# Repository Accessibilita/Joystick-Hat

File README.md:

# Joystick-HID (0.2a)
A custom open source PCB for controlling an open source wheel chair! This PCB contains all the necessary electronics for interfacing and powering all the components/peripherals that will be used to build a wheel chair human machine interface consisting of this PCB, analog JoyStick module, buttons, rotary switches, and 3D printed housing. JoyStick-HID is just one of the many PCBs being developed for our open source wheel chair electrical system we are developing with the Accessibilita project for the Mobility Independence Foundation (themif.org) !!

Functional Block Diagram of Board 

Quick Specs of the Hat:
- STM32F446RET6 100TQFP ARM Cortex M4 Microcontoller
- ARM Cortex M Serial Debu Interface/connector for in system programming and development 
- MAX3535ECWI+T RS485 Transceiver for communicating with main motor controller
- D24V22F5 2.5A 5VDC Voltage Regulator Module
- D24V22F3 2.5A 3.3VDC Voltage Regulator Module
- 24V Power Input with High Current Pheonix Contact Connector
- 8 Debug LEDs for STM32F446RET6
- Onboard Battery for STM32F446RET6 RealTime Clock
- Interface for JoyStick, JH-D202X-R2/R4 Joystick 5K https://protosupplies.com/product/jh-d202x-r2-r4-joystick-5k/
- Interface for two Rotary Switches
- Interface for 8 Momentary swiches/buttons
- Interface for LED driver board, this additional board drives LEDs in the arm wrest indicating battery level and current set speed
- STM32 will run FreeRTOS w/ Custom Processes written for all functionality with priority scheduling for safety rated functions.

This hat is intended as a developmental platform that can function in the field, it has all the features needed to control the wheel chair with additional feature that will make software development easier. The final version will be much simpler and low cost, this is only the beginning. 

2D Render of JoyStick-HID Hat in KiCAD 8.0

3D Renders of JoyStick-HID Hat in KiCAD 8.0 3D Viewer 

# Joystick-Hat (0.1a)
Version 0.1a JoyStick HID:

RPi Hat for controlling an open source wheel chair! This hat contains all the necessary electronics for interfacing and powering all the components/peripherals that will be used to control the open source wheel chair electrical system we are developing with the Accessibilita project !!

Functional Block Diagram of Board 

Quick Specs of the Hat:
- STM32F446RET6 100TQFP ARM Cortex M4 Microcontoller
- ARM Cortex M Serial Debu Interface/connector for in system programming and development 
- MAX3535ECWI+T RS485 Transceiver for communicating with main motor controller
- D24V22F5 2.5A 5VDC Voltage Regulator Module
- D24V22F3 2.5A 3.3VDC Voltage Regulator Module
- D24V22F12 2.5A 12VDC Voltage Regulator Module
- 24V Power Input with High Current Pheonix Contact Connector
- 12V Power output with High current Phoenix Contact Connector
- Rapsberry Pi 5 Running ROS2, directly power via header from 5VDC rail
- 8 Debug LEDs for STM32F446RET6
- 8 Debug LEDs for RPi 5
- Onboard Battery for STM32F446RET6 RealTime Clock
- Interface for JoyStick, JH-D202X-R2/R4 Joystick 5K https://protosupplies.com/product/jh-d202x-r2-r4-joystick-5k/
- Interface for two Rotary Switches
- Interface for 8 Momentary swiches/buttons
- Interface for LED driver board, this additional board drives LEDs in the arm wrest indicating battery level and current set speed
- STM32 will run custom FreeRTOS or ROS-Micro more to follow

This hat is intended as a developmental platform that can function in the field, it has all the features needed to control the wheel chair with additional feature that will make software development easier. The final version will be much simpler and low cost, this is only the beginning. 

2D Render of JoyStick-HID Hat in KiCAD 8.0

3D Renders of JoyStick-HID Hat in KiCAD 8.0 3D Viewer 

# Joystick-Hat (0.1a) Prototype Assembly and Test:

Notes:
assmbely notes:
- Footprint for Raspberry Pi Header connector is wrong, its 42 pins should be 40
- 10uF caps on input = footprint too small!
- C19 footprint too big
- Max chip Pin 1 legend too hard to see
- RS485 diode orientation legend not on PCB
- STM32 Pin 1 legend not there
- Header holes for DCDC regulator modules too small had to hack them on there.
- ARM Cortex M Debug Connector issues, signals are flipped around, the footprint numbering doesn't correspond to the symbol numbering.
- All DCDC Regulators Work and produce correct voltage
- Debug LEDs Work
- GPIO and ADC Interfaces Work

Firmware:
Test firmware along with instructions on how to build and run can be found here: https://github.com/Accessibilita/JoyStick-hat-firmware

## Photos 

Version 0.1a of PCB 90% of Assembled and ready for programming test

Fix for the flpped programming interface from the symbol/footprint number error

Board Hooked Up to Programming Interface with soldered on fix 

Board Powered Up Running Code

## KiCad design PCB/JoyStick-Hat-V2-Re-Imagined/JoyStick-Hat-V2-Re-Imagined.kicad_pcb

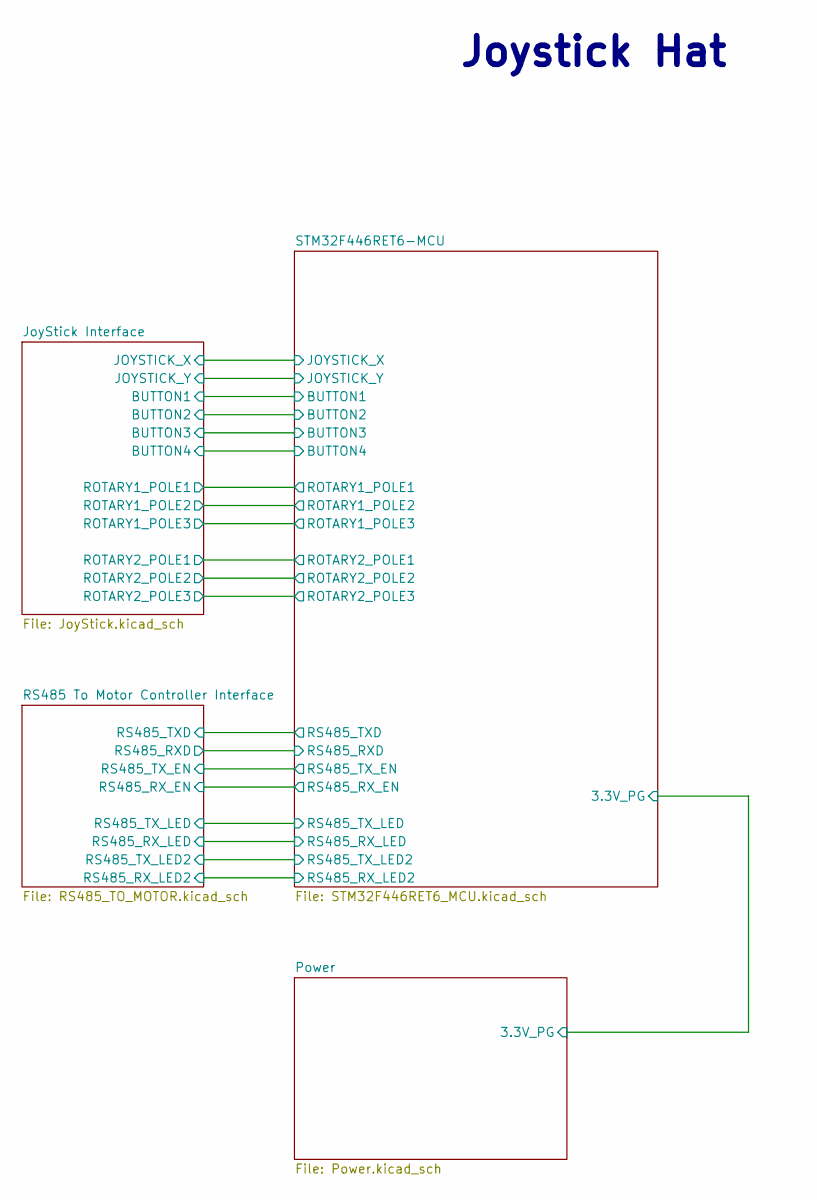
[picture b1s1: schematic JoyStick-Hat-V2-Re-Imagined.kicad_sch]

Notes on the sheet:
Joystick Hat

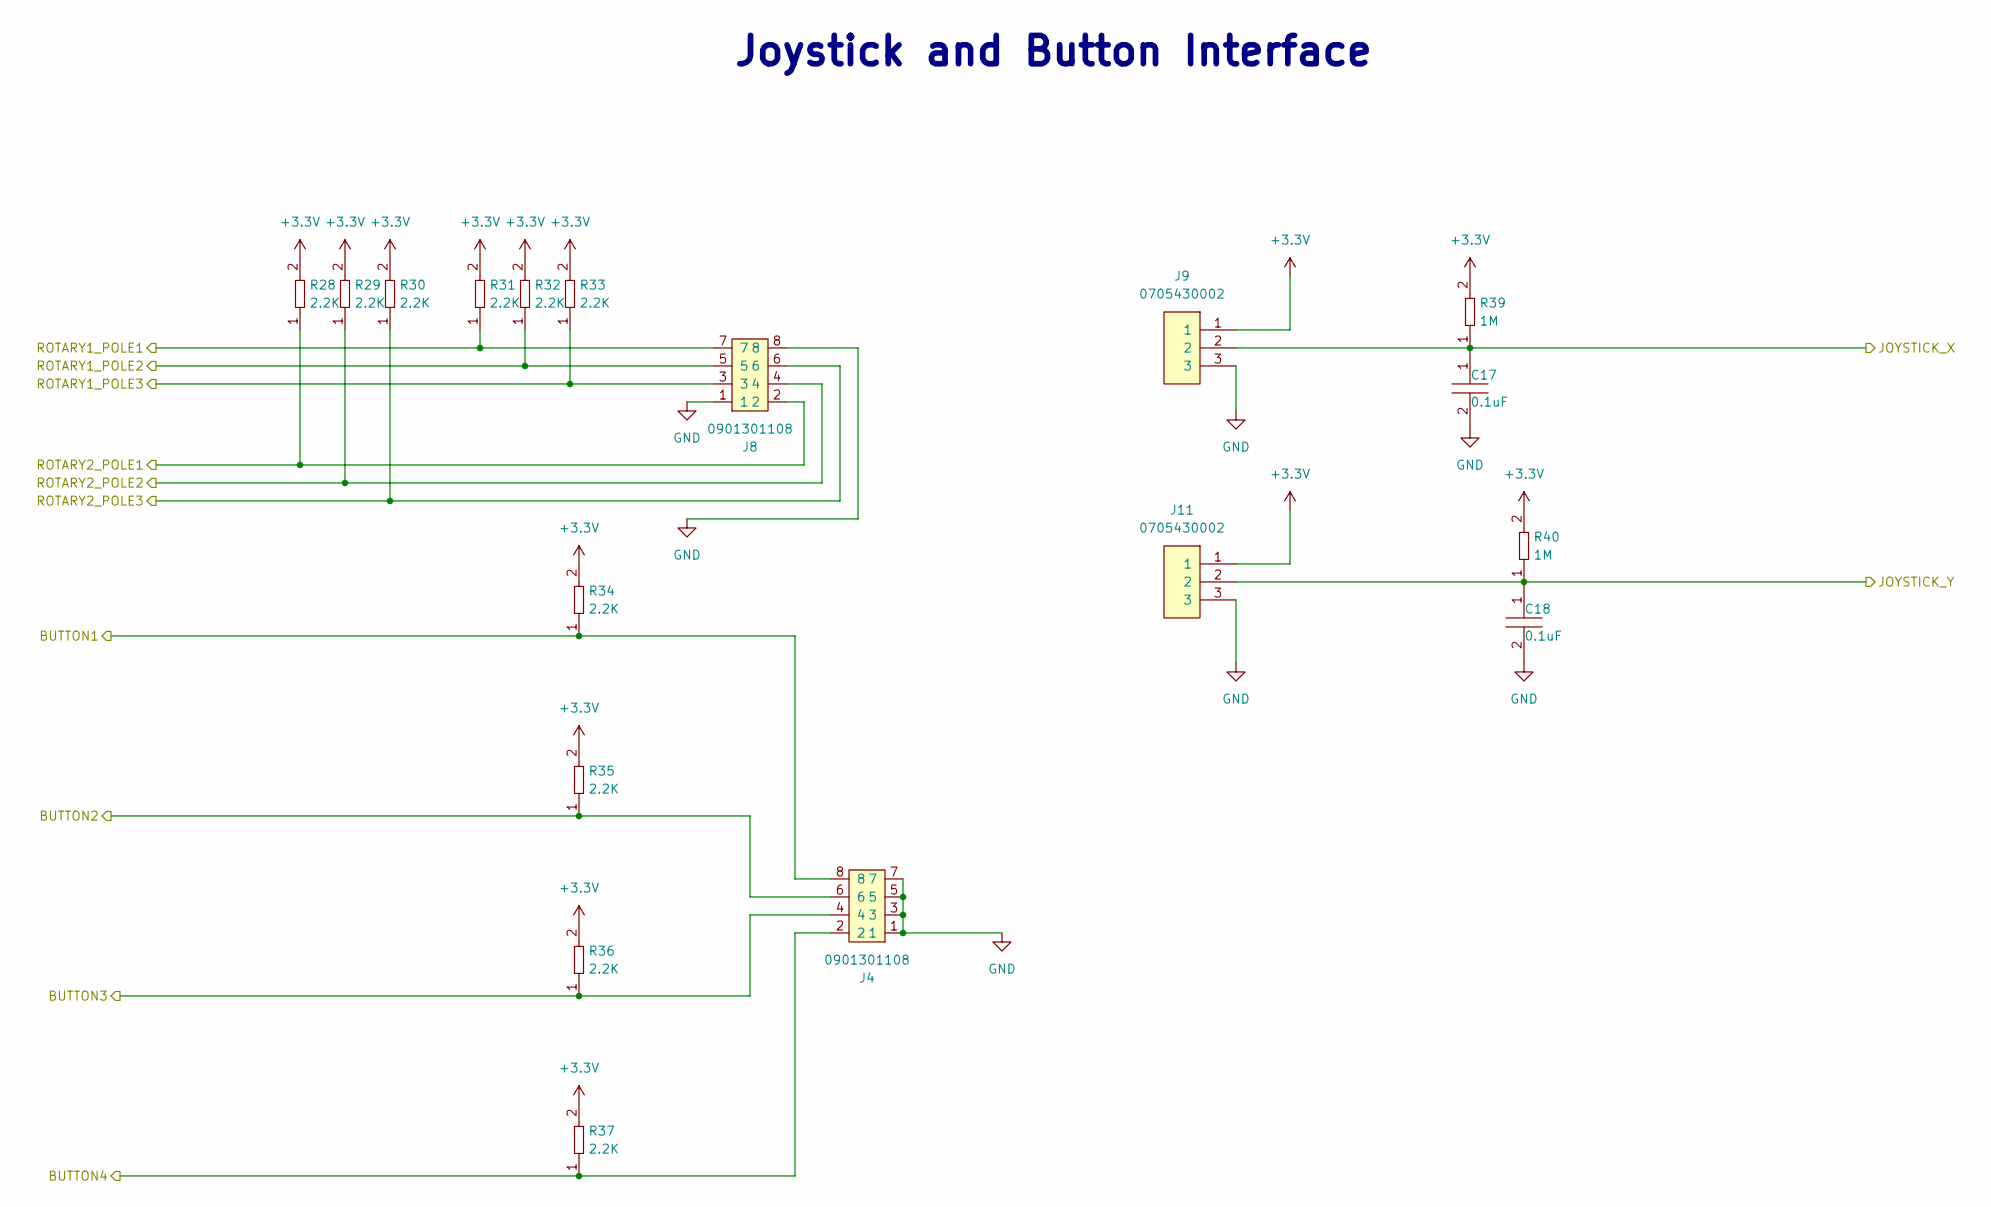
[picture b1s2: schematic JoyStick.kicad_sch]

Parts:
C17, C18: C0402C104K9PACTU; R0402; Tolerance 10%; Voltage 6.3V; MFR# C0402C104K9PACTU
J4, J8: 0901301108; CON_901301108_MOL; Tolerance *; Voltage *; MFR# 0901301108
J9, J11: 0705430002; Shrouded_Pin_Header_Straight_1x03_Pitch2.54mm; Tolerance *; Voltage 250V; MFR# 0705430002
R28, R29, R30, R31, R32, R33, R34, R35, R36, R37: RC0402FR-072K2L; R0402; Tolerance 1%; Voltage N/A; MFR# RC0402FR-072K2L
R39, R40: RT0603BRD071ML; R0603; Tolerance 1%; Voltage N/A; MFR# RT0603BRD071ML

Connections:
+3.3V: J9.1, J11.1, R28.2, R29.2, R30.2, R31.2, R32.2, R33.2, R34.2, R35.2, R36.2, R37.2, R39.2, R40.2; also elsewhere on the board
/JoyStick Interface/BUTTON1: J4.8, R34.1; also elsewhere on the board
/JoyStick Interface/BUTTON2: J4.6, R35.1; also elsewhere on the board
/JoyStick Interface/BUTTON3: J4.4, R36.1; also elsewhere on the board
/JoyStick Interface/BUTTON4: J4.2, R37.1; also elsewhere on the board
/JoyStick Interface/JOYSTICK_X: C17.1, J9.2, R39.1; also elsewhere on the board
/JoyStick Interface/JOYSTICK_Y: C18.1, J11.2, R40.1; also elsewhere on the board
/JoyStick Interface/ROTARY1_POLE1: J8.7, R31.1; also elsewhere on the board
/JoyStick Interface/ROTARY1_POLE2: J8.5, R32.1; also elsewhere on the board
/JoyStick Interface/ROTARY1_POLE3: J8.3, R33.1; also elsewhere on the board
/JoyStick Interface/ROTARY2_POLE1: J8.2, R28.1; also elsewhere on the board
/JoyStick Interface/ROTARY2_POLE2: J8.4, R29.1; also elsewhere on the board
/JoyStick Interface/ROTARY2_POLE3: J8.6, R30.1; also elsewhere on the board
GND: C17.2, C18.2, J4.1, J4.3, J4.5, J4.7, J8.1, J8.8, J9.3, J11.3; also elsewhere on the board

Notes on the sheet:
Joystick and Button Interface

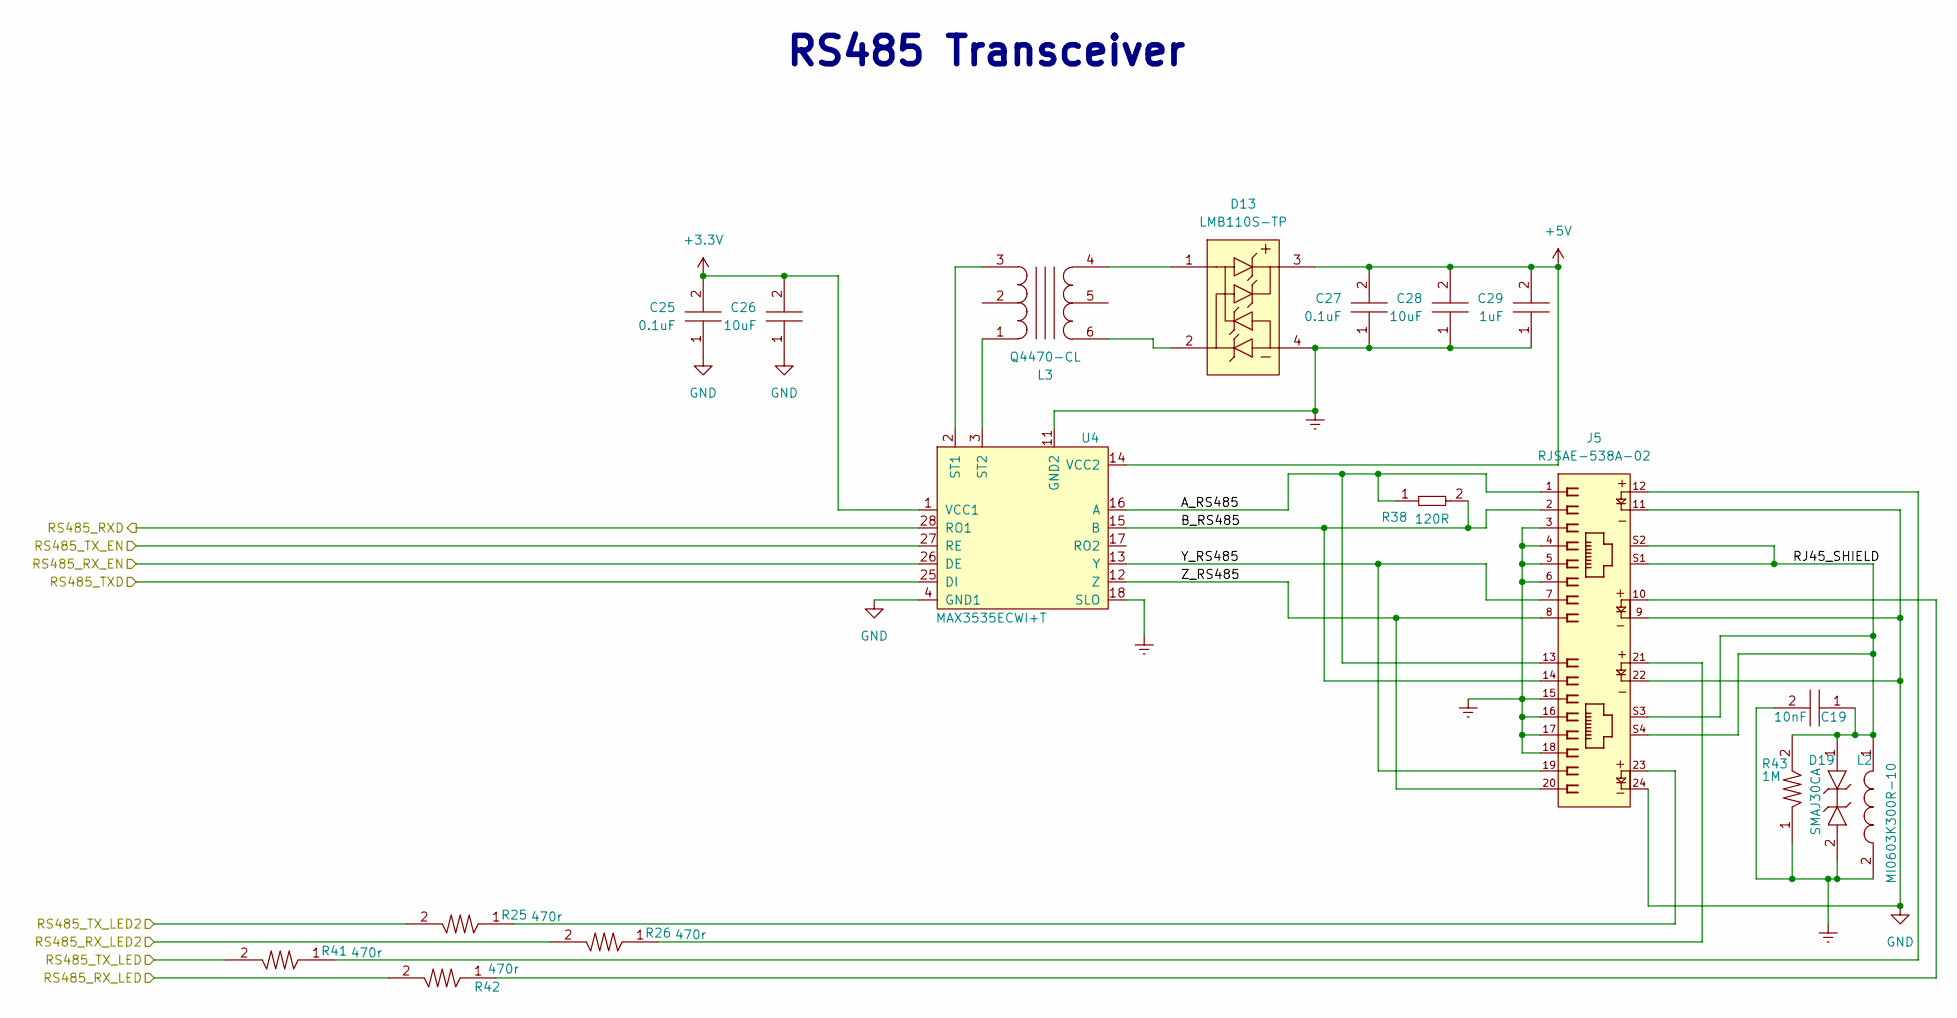
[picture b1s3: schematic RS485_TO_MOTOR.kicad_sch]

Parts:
C19: C0805C103KCRACAUTO; C0805; Tolerance 10%; Voltage 500V; MFR# C0805C103KCRACAUTO
C25, C27: CL10B104JB8NNNC; C0603; Tolerance 5%; Voltage 50V; MFR# CL10B104JB8NNNC
C26, C28: CGA5L3X5R1V106K160AB; C1206; Tolerance 10%; Voltage 35V; MFR# CGA5L3X5R1V106K160AB
C29: C1206C105K3RACAUTO; D_SOD-123; Tolerance 10%; Voltage 25V; MFR# C1206C105K3RACAUTO
D13: LMB110S-TP; Tolerance *; Voltage 850 mV @ 500 mA; MFR# LMB110S-TP
D19: SMAJ30CA; Tolerance *; Voltage 30V Clamp; MFR# SMAJ30CA
J5: RJSAE-538A-02; AMPHENOL_RJSAE538A02; Tolerance N/A; Voltage *; MFR# RJSAE-538A-02
L2: MI0603K300R-10; Tolerance *; Voltage *; MFR# MI0603K300R-10
L3: Q4470-CL; SO6_Q4470-CL_C-SIZE_COC; Tolerance *; Voltage 5V; MFR# Q4470-CL
R25, R26, R41, R42: RC0603FR-07470RL; R0603; Tolerance 1%; Voltage *; MFR# RC0603FR-07470RL
R38: AC0402FR-07120RL; R0402; Tolerance 1%; Voltage *; MFR# AC0402FR-07120RL
R43: RC1206FR-071ML; R1206; Tolerance 1%; Voltage *; MFR# RC1206FR-071ML
U4: MAX3535ECWI+T; 21-0145_W28M&plus_9_MXM; Tolerance N/A; Voltage 3-5.5V; MFR# MAX3535ECWI+T

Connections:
+3.3V: C25.2, C26.2, U4.1 (VCC1); also elsewhere on the board
+5V: C27.2, C28.2, C29.2, D13.3, U4.14 (VCC2)
/RS485 To Motor Controller Interface/A_RS485: J5.1, J5.13, R38.1, U4.16 (A)
/RS485 To Motor Controller Interface/B_RS485: J5.2, J5.14, R38.2, U4.15 (B)
/RS485 To Motor Controller Interface/RJ45_SHIELD: C19.1, D19.1, J5.S1, J5.S2, J5.S3, J5.S4, L2.1, R43.2
/RS485 To Motor Controller Interface/RS485_RXD: U4.28 (RO1); also elsewhere on the board
/RS485 To Motor Controller Interface/RS485_RX_EN: U4.26 (DE); also elsewhere on the board
/RS485 To Motor Controller Interface/RS485_RX_LED: R42.2; also elsewhere on the board
/RS485 To Motor Controller Interface/RS485_RX_LED2: R26.2; also elsewhere on the board
/RS485 To Motor Controller Interface/RS485_TXD: U4.25 (DI); also elsewhere on the board
/RS485 To Motor Controller Interface/RS485_TX_EN: U4.27 (RE); also elsewhere on the board
/RS485 To Motor Controller Interface/RS485_TX_LED: R41.2; also elsewhere on the board
/RS485 To Motor Controller Interface/RS485_TX_LED2: R25.2; also elsewhere on the board
/RS485 To Motor Controller Interface/Y_RS485: J5.7, J5.19, U4.13 (Y)
/RS485 To Motor Controller Interface/Z_RS485: J5.8, J5.20, U4.12 (Z)
Earth: C19.2, C27.1, C28.1, C29.1, D13.4, D19.2, J5.3, J5.4, J5.5, J5.6, J5.15, J5.16, J5.17, J5.18, L2.2, R43.1, U4.11 (GND2), U4.18 (SLO)
GND: C25.1, C26.1, J5.9, J5.11, J5.22, J5.24, U4.4 (GND1); also elsewhere on the board
unnamed: D13.1, L3.4
unnamed: D13.2, L3.6
unnamed: J5.10, R42.1
unnamed: J5.12, R41.1
unnamed: J5.21, R26.1
unnamed: J5.23, R25.1
unnamed: L3.3, U4.2 (ST1)
unnamed: L3.1, U4.3 (ST2)

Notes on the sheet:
RS485 Transceiver

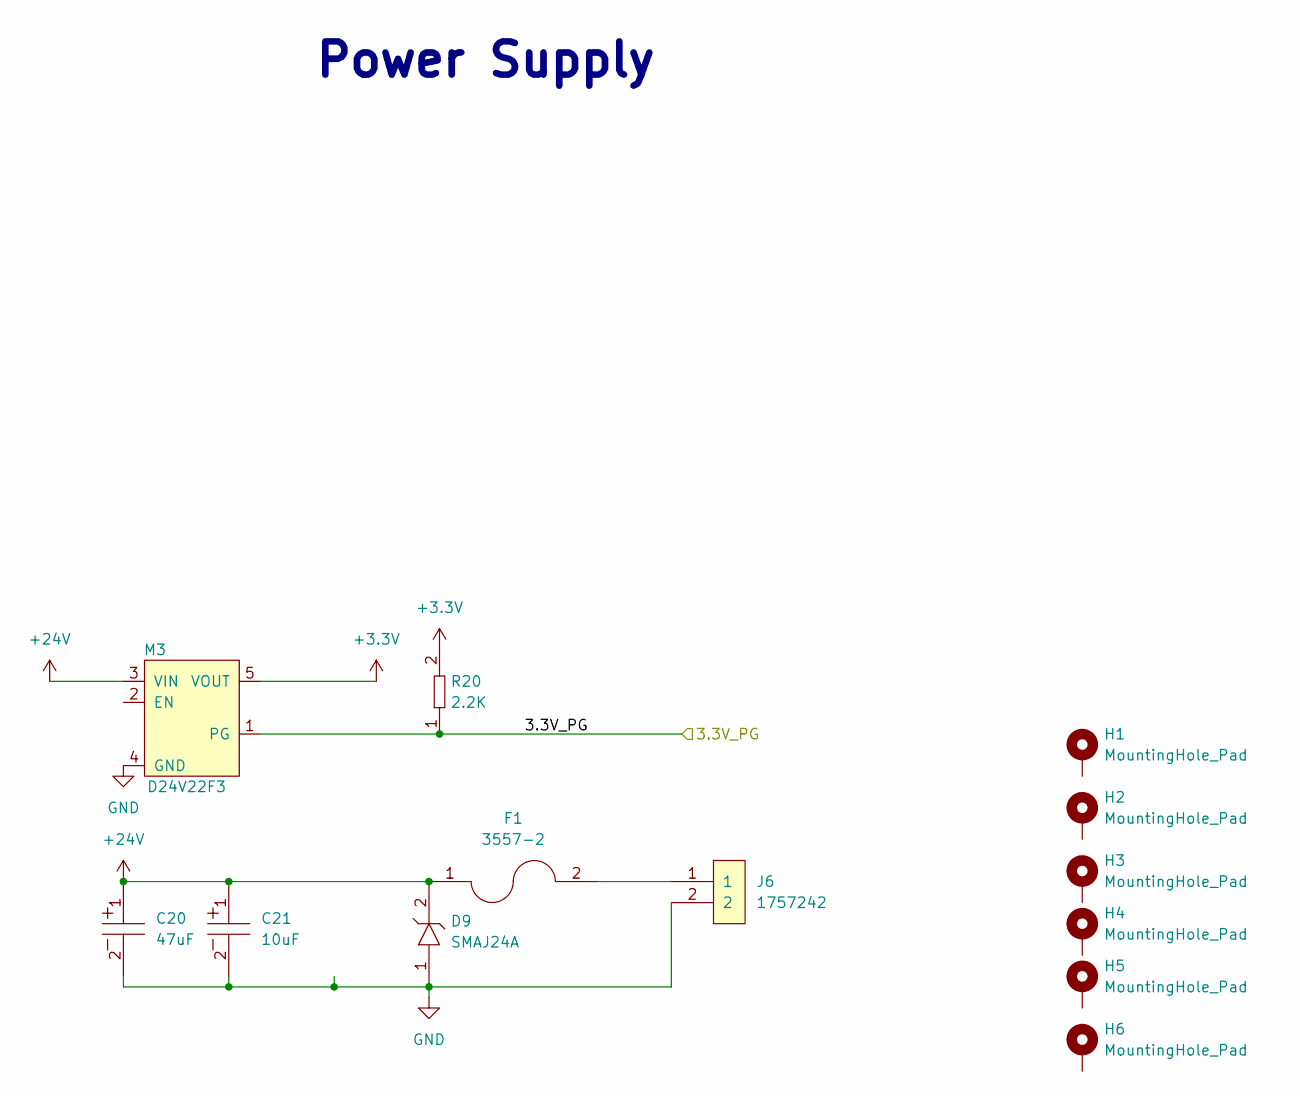
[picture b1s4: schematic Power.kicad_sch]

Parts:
C20: UUQ1H470MCL1GS; CP_Elec_8x10; Tolerance 20%; Voltage 50V; MFR# UUQ1H470MCL1GS
C21: UUQ1H100MCL1GB; CAP_UUQ_6P3X5P4_NCH; Tolerance 20%; Voltage 50V; MFR# UUQ1H100MCL1GB
D9: SMAJ24A; SMAJ; Tolerance *; Voltage 24V RS, 26.7V VB, 38.9V Clamp; MFR# SMAJ24A
F1: 3557-2; FUSE_3557-2; Tolerance *; Voltage 500V; MFR# 3557-2
H1, H2, H3, H4, H5, H6: MountingHole_Pad; RPI_HAT_HOLE
J6: 1757242; PhoenixContact_MSTBA-G_02x5.08mm_Angled; Tolerance *; Voltage 300V; MFR# 1757242
M3: D24V22F3; D24V22F12; Tolerance N/A; Voltage 36V IN 3.3V OUT; MFR# D24V22F3
R20: RC0603FR-072K2L; R0603; Tolerance 1%; Voltage N/A; MFR# RC0603FR-072K2L

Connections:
+3.3V: M3.5 (VOUT), R20.2; also elsewhere on the board
+24V: C20.1, C21.1, D9.2, F1.1, M3.3 (VIN)
/Power/3.3V_PG: M3.1 (PG), R20.1; also elsewhere on the board
GND: C20.2, C21.2, D9.1, J6.2, M3.4 (GND); also elsewhere on the board
unnamed: F1.2, J6.1

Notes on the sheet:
Power Supply

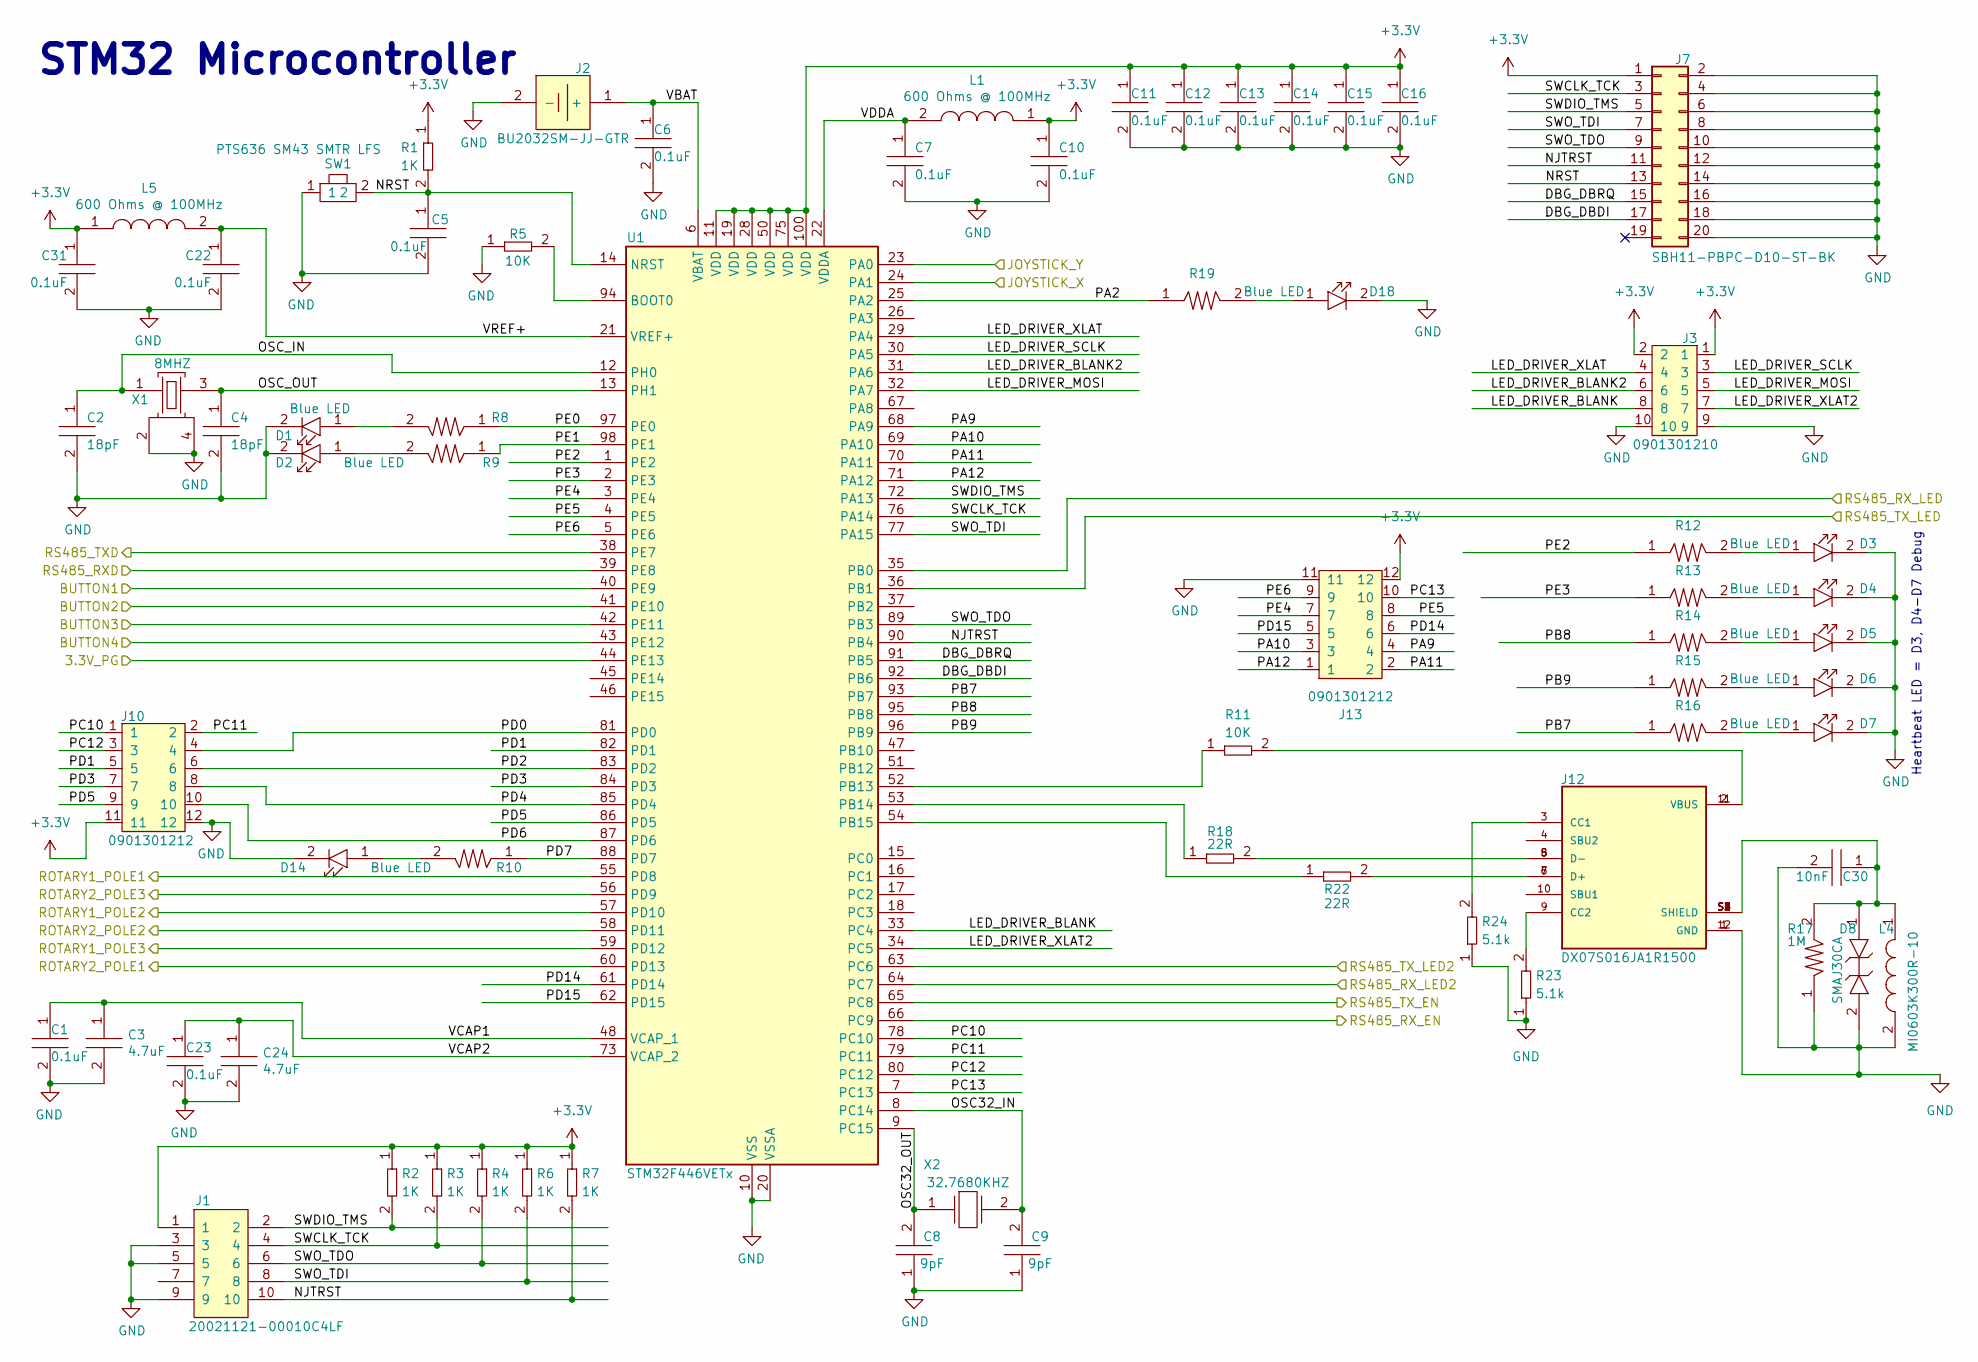
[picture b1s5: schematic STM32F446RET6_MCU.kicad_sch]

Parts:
C1, C5, C6, C7, C10, C11, C12, C13, C14, C15, C16, C22, C23, C31: C0402C104K9PACTU; R0402; Tolerance 10%; Voltage 6.3V; MFR# C0402C104K9PACTU
C2, C4: GCM1555C1H180GA16D; C0402; Tolerance 2%; Voltage 50V; MFR# GCM1555C1H180GA16D
C3, C24: GRM155R60J475ME47D; C0402; Tolerance 20%; Voltage 6.3V; MFR# GRM155R60J475ME47D
C8, C9: CL05C090CB5NNNC; C0402; Tolerance ±0.25pF; Voltage 50V; MFR# CL05C090CB5NNNC
C30: C0805C103KCRACAUTO; C0805; Tolerance 10%; Voltage 500V; MFR# C0805C103KCRACAUTO
D1, D2, D3, D4, D5, D6, D7, D14, D18: LTST-C194TBKT; LED0603; Tolerance *; Voltage 3.3V; MFR# LTST-C194TBKT
D8: SMAJ30CA; Tolerance *; Voltage 30V Clamp; MFR# SMAJ30CA
J1: 20021121-00010C4LF; Tolerance *; Voltage *; MFR# 20021121-00010C4LF
J2: BU2032SM-JJ-GTR; Tolerance *; Voltage 3.3V; MFR# BU2032SM-JJ-GTR
J3: 0901301210; CON_901301210_MOL; Tolerance *; Voltage *; MFR# 0901301210
J7: SBH11-PBPC-D10-ST-BK; SULLINS_SBH11-PBPC-D10-ST-BK; Tolerance *; Voltage *; MFR# SBH11-PBPC-D10-ST-BK
J10, J13: 0901301212; CON_901301212_MOL; Tolerance *; Voltage *; MFR# 0901301212
J12: DX07S016JA1R1500; JAE_DX07S016JA1R1500; Tolerance *; Voltage 20V; MFR# DX07S016JA1R1500
L1, L5: BLM15HG601SN1D; Tolerance *; Voltage *; MFR# BLM15HG601SN1D
L4: MI0603K300R-10; Tolerance *; Voltage *; MFR# MI0603K300R-10
R1, R2, R3, R4, R6, R7: RC0402FR-071KL; R0402; Tolerance 1%; Voltage *; MFR# RC0402FR-071KL
R5, R11: RC0402FR-0710KL; R0402; Tolerance 1%; Voltage *; MFR# RC0402FR-0710KL
R8, R9, R10, R12, R13, R14, R15, R16, R19: RC0603FR-07470RL; R0603; Tolerance 1%; Voltage *; MFR# RC0603FR-07470RL
R17: RC1206FR-071ML; R1206; Tolerance 1%; Voltage *; MFR# RC1206FR-071ML
R18, R22: RC0402FR-0722RL; R0402; Tolerance 1%; Voltage *; MFR# RC0402FR-0722RL
R23, R24: RC0402FR-075K1L; R0402; Tolerance 1%; Voltage N/A; MFR# RC0402FR-075K1L
SW1: PTS636 SM43 SMTR LFS; Tolerance *; Voltage 12V; MFR# PTS636 SM43 SMTR LFS
U1: STM32F446VETx; LQFP-100_14x14mm_P0.5mm
X1: ABM3B-8.000MHZ-B2-T; ABM3B8.000MHZB2T; Tolerance *; Voltage *; MFR# ABM3B-8.000MHZ-B2-T
X2: ABS07-32.768KHZ-9-T; Tolerance *; Voltage *; MFR# ABS07-32.768KHZ-9-T

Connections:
+3.3V: C10.1, C11.1, C12.1, C13.1, C14.1, C15.1, C16.1, C31.1, J1.1, J3.1, J3.2, J7.1, J10.11, J13.12, L1.1, L5.1, R1.1, R2.1, R3.1, R4.1, R6.1, R7.1, U1.11 (VDD), U1.19 (VDD), U1.28 (VDD), U1.50 (VDD), U1.75 (VDD), U1.100 (VDD); also elsewhere on the board
/JoyStick Interface/BUTTON1: U1.40 (PE9); also elsewhere on the board
/JoyStick Interface/BUTTON2: U1.41 (PE10); also elsewhere on the board
/JoyStick Interface/BUTTON3: U1.42 (PE11); also elsewhere on the board
/JoyStick Interface/BUTTON4: U1.43 (PE12); also elsewhere on the board
/JoyStick Interface/JOYSTICK_X: U1.24 (PA1); also elsewhere on the board
/JoyStick Interface/JOYSTICK_Y: U1.23 (PA0); also elsewhere on the board
/JoyStick Interface/ROTARY1_POLE1: U1.55 (PD8); also elsewhere on the board
/JoyStick Interface/ROTARY1_POLE2: U1.57 (PD10); also elsewhere on the board
/JoyStick Interface/ROTARY1_POLE3: U1.59 (PD12); also elsewhere on the board
/JoyStick Interface/ROTARY2_POLE1: U1.60 (PD13); also elsewhere on the board
/JoyStick Interface/ROTARY2_POLE2: U1.58 (PD11); also elsewhere on the board
/JoyStick Interface/ROTARY2_POLE3: U1.56 (PD9); also elsewhere on the board
/Power/3.3V_PG: U1.44 (PE13); also elsewhere on the board
/RS485 To Motor Controller Interface/RS485_RXD: U1.39 (PE8); also elsewhere on the board
/RS485 To Motor Controller Interface/RS485_RX_EN: U1.66 (PC9); also elsewhere on the board
/RS485 To Motor Controller Interface/RS485_RX_LED: U1.35 (PB0); also elsewhere on the board
/RS485 To Motor Controller Interface/RS485_RX_LED2: U1.64 (PC7); also elsewhere on the board
/RS485 To Motor Controller Interface/RS485_TXD: U1.38 (PE7); also elsewhere on the board
/RS485 To Motor Controller Interface/RS485_TX_EN: U1.65 (PC8); also elsewhere on the board
/RS485 To Motor Controller Interface/RS485_TX_LED: U1.36 (PB1); also elsewhere on the board
/RS485 To Motor Controller Interface/RS485_TX_LED2: U1.63 (PC6); also elsewhere on the board
/STM32F446RET6-MCU/5V_PG: U1.45 (PE14)
/STM32F446RET6-MCU/12V_PG: U1.46 (PE15)
/STM32F446RET6-MCU/DBG_DBDI: J7.17, U1.92 (PB6)
/STM32F446RET6-MCU/DBG_DBRQ: J7.15, U1.91 (PB5)
/STM32F446RET6-MCU/LED_DRIVER_BLANK: J3.8, U1.33 (PC4)
/STM32F446RET6-MCU/LED_DRIVER_BLANK2: J3.6, U1.31 (PA6)
/STM32F446RET6-MCU/LED_DRIVER_MOSI: J3.5, U1.32 (PA7)
/STM32F446RET6-MCU/LED_DRIVER_SCLK: J3.3, U1.30 (PA5)
/STM32F446RET6-MCU/LED_DRIVER_XLAT: J3.4, U1.29 (PA4)
/STM32F446RET6-MCU/LED_DRIVER_XLAT2: J3.7, U1.34 (PC5)
/STM32F446RET6-MCU/NJTRST: J1.10, J7.11, R7.2, U1.90 (PB4)
/STM32F446RET6-MCU/NRST: C5.1, J7.13, R1.2, SW1.2, U1.14 (NRST)
/STM32F446RET6-MCU/OSC32_IN: C9.2, U1.8 (PC14), X2.2
/STM32F446RET6-MCU/OSC32_OUT: C8.2, U1.9 (PC15), X2.1
/STM32F446RET6-MCU/OSC_IN: C2.1, U1.12 (PH0), X1.1
/STM32F446RET6-MCU/OSC_OUT: C4.1, U1.13 (PH1), X1.3
/STM32F446RET6-MCU/PA2: R19.1, U1.25 (PA2)
/STM32F446RET6-MCU/PA9: J13.4, U1.68 (PA9)
/STM32F446RET6-MCU/PA10: J13.3, U1.69 (PA10)
/STM32F446RET6-MCU/PA11: J13.2, U1.70 (PA11)
/STM32F446RET6-MCU/PA12: J13.1, U1.71 (PA12)
/STM32F446RET6-MCU/PB7: R16.1, U1.93 (PB7)
/STM32F446RET6-MCU/PB8: R14.1, U1.95 (PB8)
/STM32F446RET6-MCU/PB9: R15.1, U1.96 (PB9)
/STM32F446RET6-MCU/PC10: J10.1, U1.78 (PC10)
/STM32F446RET6-MCU/PC11: J10.2, U1.79 (PC11)
/STM32F446RET6-MCU/PC12: J10.3, U1.80 (PC12)
/STM32F446RET6-MCU/PC13: J13.10, U1.7 (PC13)
/STM32F446RET6-MCU/PD0: J10.4, U1.81 (PD0)
/STM32F446RET6-MCU/PD1: J10.5, U1.82 (PD1)
/STM32F446RET6-MCU/PD2: J10.6, U1.83 (PD2)
/STM32F446RET6-MCU/PD3: J10.7, U1.84 (PD3)
/STM32F446RET6-MCU/PD4: J10.8, U1.85 (PD4)
/STM32F446RET6-MCU/PD5: J10.9, U1.86 (PD5)
/STM32F446RET6-MCU/PD6: J10.10, U1.87 (PD6)
/STM32F446RET6-MCU/PD7: R10.1, U1.88 (PD7)
/STM32F446RET6-MCU/PD14: J13.6, U1.61 (PD14)
/STM32F446RET6-MCU/PD15: J13.5, U1.62 (PD15)
/STM32F446RET6-MCU/PE0: R8.1, U1.97 (PE0)
/STM32F446RET6-MCU/PE1: R9.1, U1.98 (PE1)
/STM32F446RET6-MCU/PE2: R12.1, U1.1 (PE2)
/STM32F446RET6-MCU/PE3: R13.1, U1.2 (PE3)
/STM32F446RET6-MCU/PE4: J13.7, U1.3 (PE4)
/STM32F446RET6-MCU/PE5: J13.8, U1.4 (PE5)
/STM32F446RET6-MCU/PE6: J13.9, U1.5 (PE6)
/STM32F446RET6-MCU/SWCLK_TCK: J1.4, J7.3, R3.2, U1.76 (PA14)
/STM32F446RET6-MCU/SWDIO_TMS: J1.2, J7.5, R2.2, U1.72 (PA13)
/STM32F446RET6-MCU/SWO_TDI: J1.8, J7.7, R6.2, U1.77 (PA15)
/STM32F446RET6-MCU/SWO_TDO: J1.6, J7.9, R4.2, U1.89 (PB3)
/STM32F446RET6-MCU/VBAT: C6.1, J2.1 (+), U1.6 (VBAT)
/STM32F446RET6-MCU/VCAP1: C1.1, C3.1, U1.48 (VCAP_1)
/STM32F446RET6-MCU/VCAP2: C23.1, C24.1, U1.73 (VCAP_2)
/STM32F446RET6-MCU/VDDA: C7.1, L1.2, U1.22 (VDDA)
/STM32F446RET6-MCU/VREF+: C22.1, L5.2, U1.21 (VREF+)
GND: C1.2, C2.2, C3.2, C4.2, C5.2, C6.2, C7.2, C8.1, C9.1, C10.2, C11.2, C12.2, C13.2, C14.2, C15.2, C16.2, C22.2, C23.2, C24.2, C30.2, C31.2, D1.2, D2.2, D3.2, D4.2, D5.2, D6.2, D7.2, D8.2, D14.2, D18.2, J1.3, J1.5, J1.9, J2.2 (-), J3.9, J3.10, J7.2, J7.4, J7.6, J7.8, J7.10, J7.12, J7.14, J7.16, J7.18, J7.20, J10.12, J12.1 (GND), J12.12 (GND), J13.11, L4.2, R5.1, R17.1, R23.1, R24.1, SW1.1, U1.10 (VSS), U1.20 (VSSA), U1.27 (VSS), U1.49 (VSS), U1.74 (VSS), U1.99 (VSS), X1.2, X1.4; also elsewhere on the board
unnamed: C30.1, D8.1, J12.S1 (SHIELD), J12.S2 (SHIELD), J12.S3 (SHIELD), J12.S4 (SHIELD), J12.S5 (SHIELD), J12.S6 (SHIELD), L4.1, R17.2
unnamed: D1.1, R8.2
unnamed: D2.1, R9.2
unnamed: D3.1, R12.2
unnamed: D4.1, R13.2
unnamed: D5.1, R14.2
unnamed: D6.1, R15.2
unnamed: D7.1, R16.2
unnamed: D14.1, R10.2
unnamed: D18.1, R19.2
unnamed: J12.3 (CC1), R24.2
unnamed: J12.9 (CC2), R23.2
unnamed: J12.6 (D+), J12.7 (D+), R22.2
unnamed: J12.5 (D-), J12.8 (D-), R18.2
unnamed: J12.2 (VBUS), J12.11 (VBUS), R11.2
unnamed: R5.2, U1.94 (BOOT0)
unnamed: R11.1, U1.52 (PB13)
unnamed: R18.1, U1.53 (PB14)
unnamed: R22.1, U1.54 (PB15)

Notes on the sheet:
Heartbeat LED = D3, D4-D7 Debug
STM32 Microcontroller

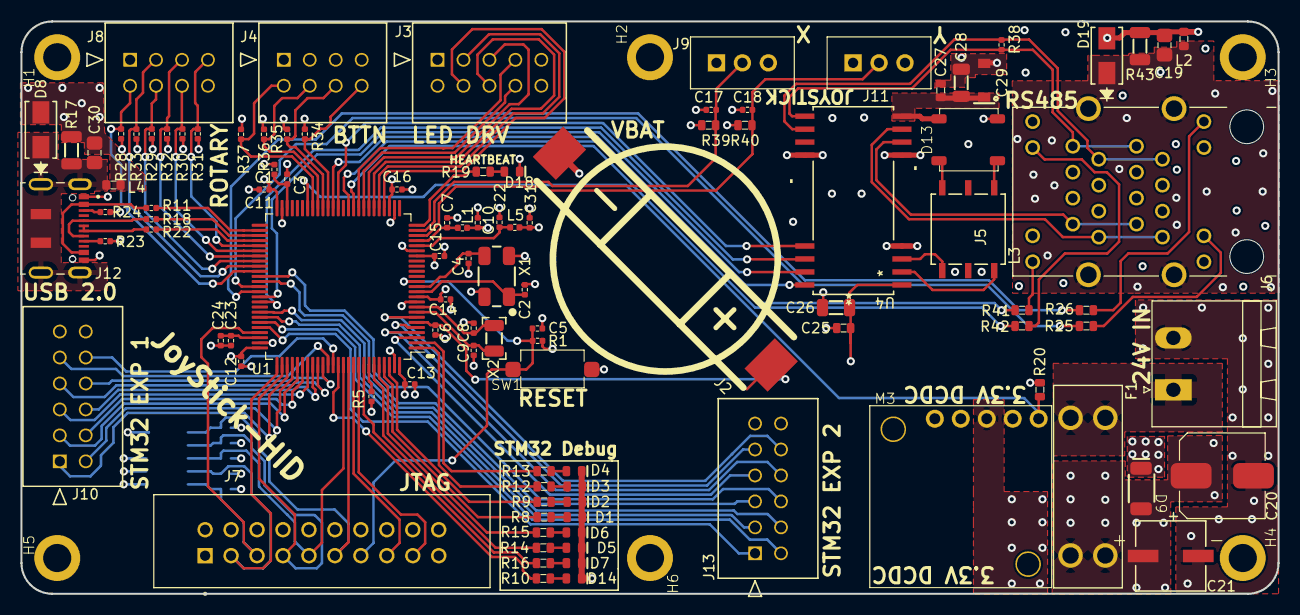
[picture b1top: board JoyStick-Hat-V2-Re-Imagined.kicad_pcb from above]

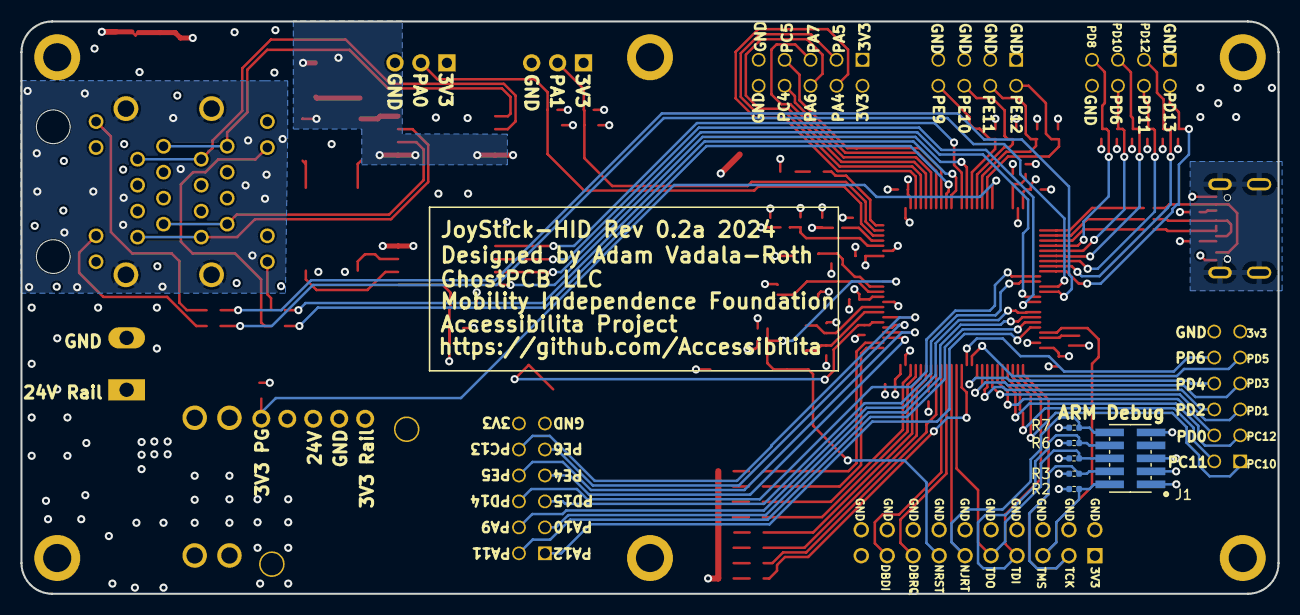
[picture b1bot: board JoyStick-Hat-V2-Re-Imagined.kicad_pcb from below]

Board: 4 copper layers, 123.0 x 56.0 mm, 116 parts (6 on the bottom side), 111 nets.

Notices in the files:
parts and their libraries:
Copyright 2016 Accelerated Designs. All rights reserved.
